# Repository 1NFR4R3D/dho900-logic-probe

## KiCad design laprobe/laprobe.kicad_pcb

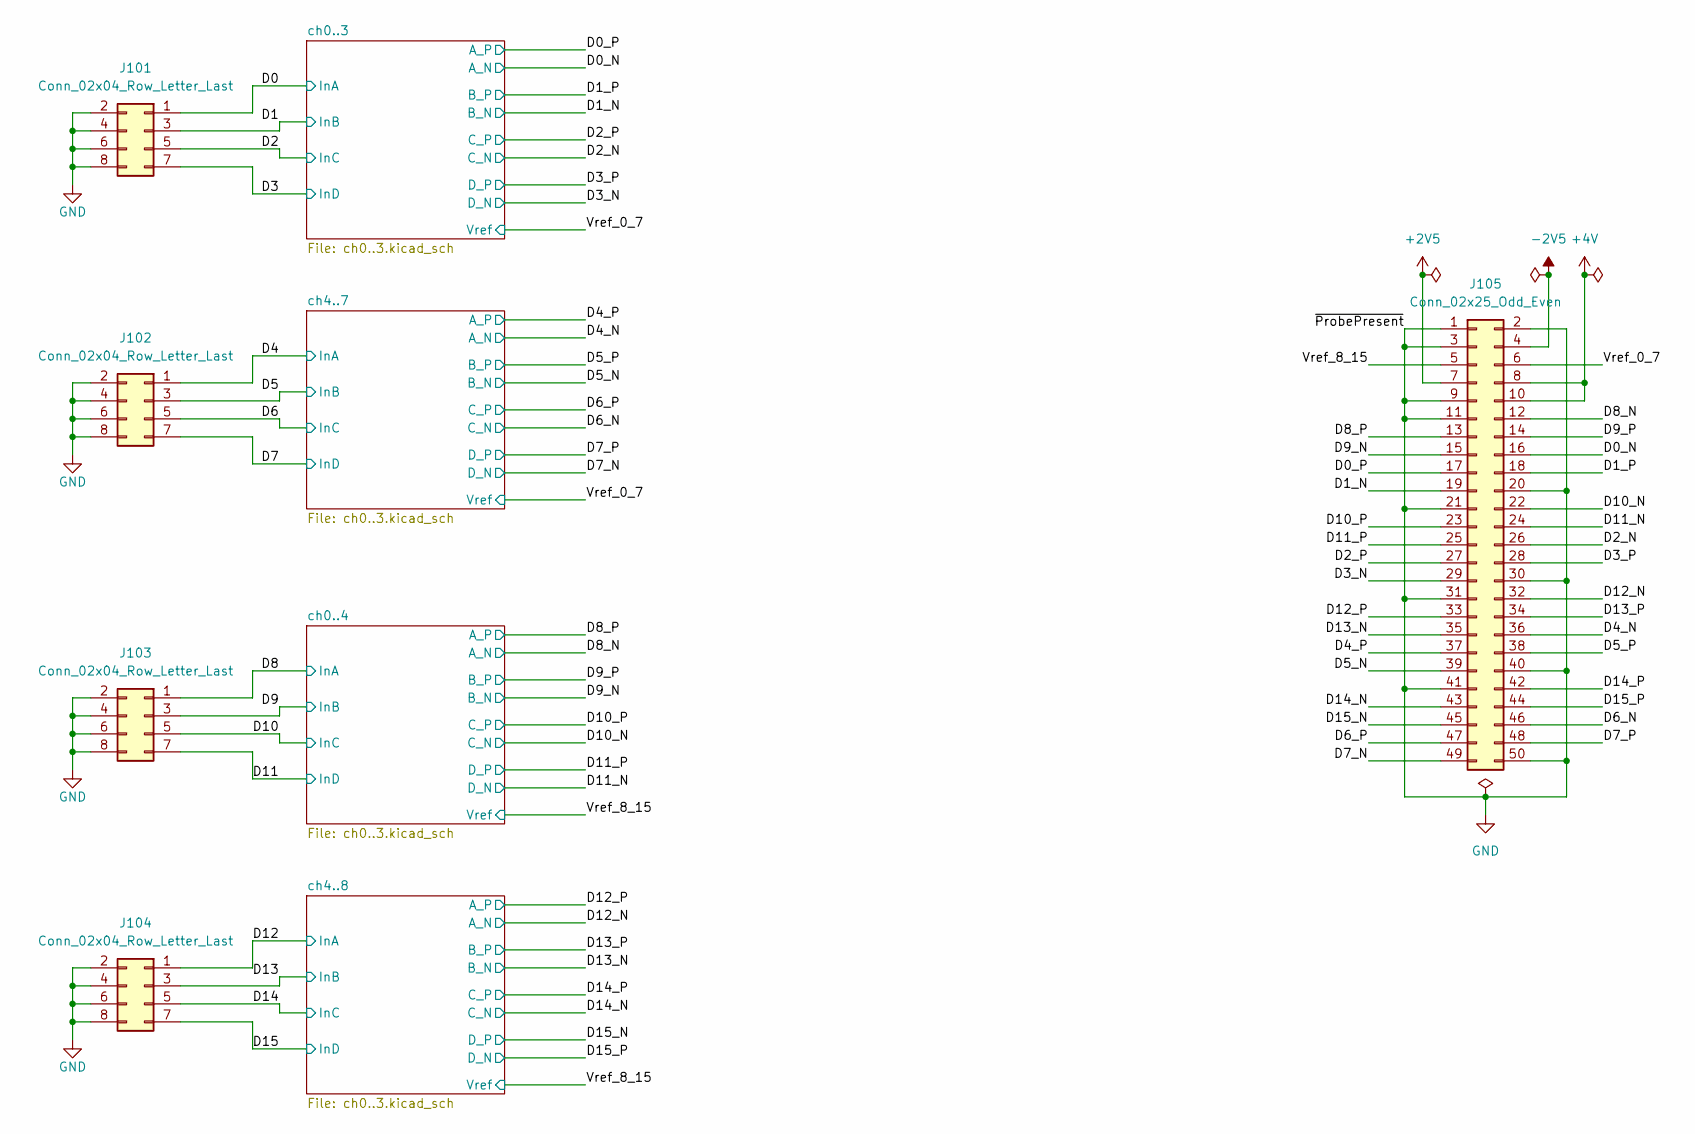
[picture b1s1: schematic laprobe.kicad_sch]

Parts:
J101, J102, J103, J104: Conn_02x04_Row_Letter_Last; PinHeader_2x04_P2.54mm_Vertical
J105: Conn_02x25_Odd_Even; IDC-Header_2x25_P2.54mm_Vertical

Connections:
+2V5: J105.7; also elsewhere on the board
+4V: J105.8, J105.10; also elsewhere on the board
-2V5: J105.4; also elsewhere on the board
/D0: J101.1; also elsewhere on the board
/D0_N: J105.16; also elsewhere on the board
/D0_P: J105.17; also elsewhere on the board
/D1: J101.3; also elsewhere on the board
/D1_N: J105.19; also elsewhere on the board
/D1_P: J105.18; also elsewhere on the board
/D2: J101.5; also elsewhere on the board
/D2_N: J105.26; also elsewhere on the board
/D2_P: J105.27; also elsewhere on the board
/D3: J101.7; also elsewhere on the board
/D3_N: J105.29; also elsewhere on the board
/D3_P: J105.28; also elsewhere on the board
/D4: J102.1; also elsewhere on the board
/D4_N: J105.36; also elsewhere on the board
/D4_P: J105.37; also elsewhere on the board
/D5: J102.3; also elsewhere on the board
/D5_N: J105.39; also elsewhere on the board
/D5_P: J105.38; also elsewhere on the board
/D6: J102.5; also elsewhere on the board
/D6_N: J105.46; also elsewhere on the board
/D6_P: J105.47; also elsewhere on the board
/D7: J102.7; also elsewhere on the board
/D7_N: J105.49; also elsewhere on the board
/D7_P: J105.48; also elsewhere on the board
/D8: J103.1; also elsewhere on the board
/D8_N: J105.12; also elsewhere on the board
/D8_P: J105.13; also elsewhere on the board
/D9: J103.3; also elsewhere on the board
/D9_N: J105.15; also elsewhere on the board
/D9_P: J105.14; also elsewhere on the board
/D10: J103.5; also elsewhere on the board
/D10_N: J105.22; also elsewhere on the board
/D10_P: J105.23; also elsewhere on the board
/D11: J103.7; also elsewhere on the board
/D11_N: J105.24; also elsewhere on the board
/D11_P: J105.25; also elsewhere on the board
/D12: J104.1; also elsewhere on the board
/D12_N: J105.32; also elsewhere on the board
/D12_P: J105.33; also elsewhere on the board
/D13: J104.3; also elsewhere on the board
/D13_N: J105.35; also elsewhere on the board
/D13_P: J105.34; also elsewhere on the board
/D14: J104.5; also elsewhere on the board
/D14_N: J105.43; also elsewhere on the board
/D14_P: J105.42; also elsewhere on the board
/D15: J104.7; also elsewhere on the board
/D15_N: J105.45; also elsewhere on the board
/D15_P: J105.44; also elsewhere on the board
/Vref_0_7: J105.6; also elsewhere on the board
/Vref_8_15: J105.5; also elsewhere on the board
GND: J101.2, J101.4, J101.6, J101.8, J102.2, J102.4, J102.6, J102.8, J103.2, J103.4, J103.6, J103.8, J104.2, J104.4, J104.6, J104.8, J105.1, J105.2, J105.3, J105.9, J105.11, J105.20, J105.21, J105.30, J105.31, J105.40, J105.41, J105.50; also elsewhere on the board

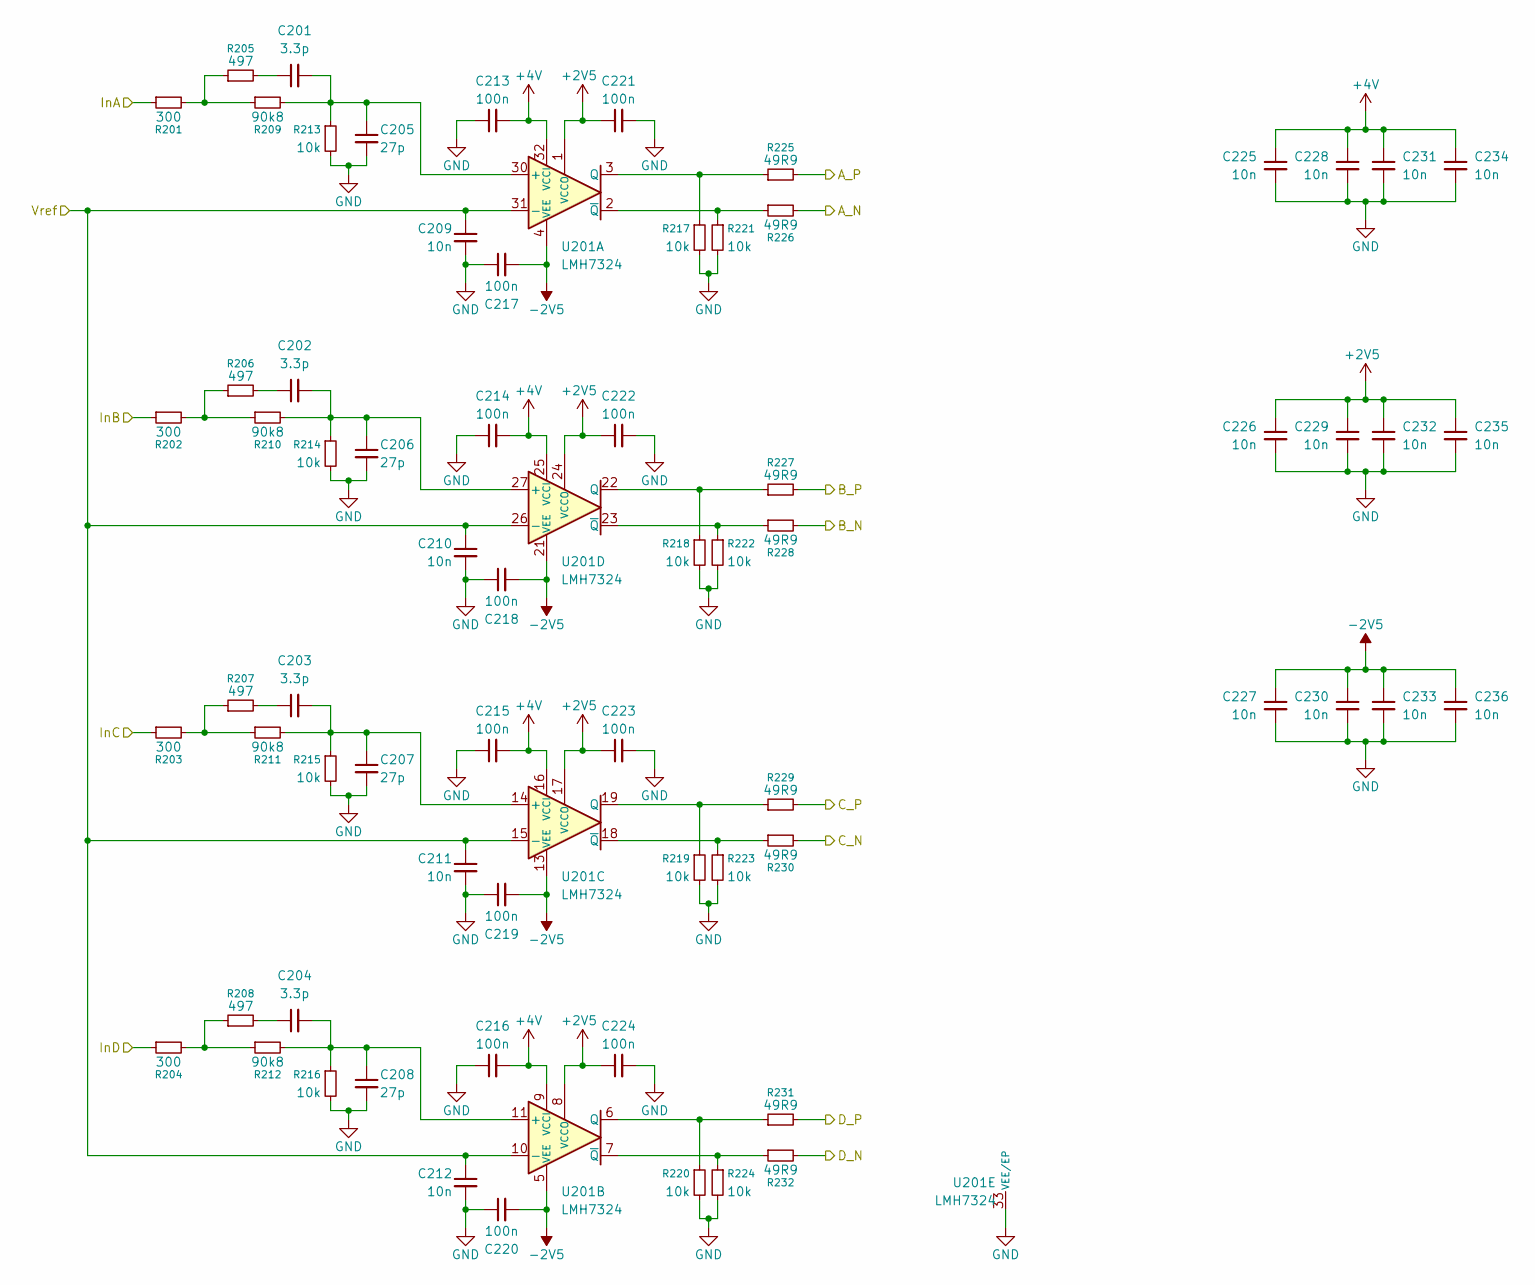
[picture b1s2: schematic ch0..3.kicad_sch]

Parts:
C201, C202, C203, C204: 3.3p; C_0603_1608Metric
C205, C206, C207, C208: 27p; C_0603_1608Metric
C209, C210, C211, C212, C225, C226, C227, C228, C229, C230, C231, C232, C233, C234, C235, C236: 10n; C_0603_1608Metric
C213, C214, C215, C216, C217, C218, C219, C220, C221, C222, C223, C224: 100n; C_0603_1608Metric
R201, R202, R203, R204: 300; R_0603_1608Metric
R205, R206, R207, R208: 497; R_0603_1608Metric
R209, R210, R211, R212: 90k8; R_0603_1608Metric
R213, R214, R215, R216, R217, R218, R219, R220, R221, R222, R223, R224: 10k; R_0603_1608Metric
R225, R226, R227, R228, R229, R230, R231, R232: 49R9; R_0603_1608Metric
U201: LMH7324; WQFN-32-1EP_5x5mm_P0.5mm_EP3.1x3.1mm

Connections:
+2V5: C221.1, C222.1, C223.1, C224.1, C226.1, C229.1, C232.1, C235.1, U201.1 (VCCO), U201.8 (VCCO), U201.17 (VCCO), U201.24 (VCCO); also elsewhere on the board
+4V: C213.2, C214.2, C215.2, C216.2, C225.1, C228.1, C231.1, C234.1, U201.9 (VCCI), U201.16 (VCCI), U201.25 (VCCI), U201.32 (VCCI); also elsewhere on the board
-2V5: C217.2, C218.2, C219.2, C220.2, C227.1, C230.1, C233.1, C236.1, U201.4 (VEE), U201.5 (VEE), U201.12 (VEE), U201.13 (VEE), U201.20 (VEE), U201.21 (VEE), U201.28 (VEE), U201.29 (VEE); also elsewhere on the board
/D0: R201.1; also elsewhere on the board
/D0_N: R226.2; also elsewhere on the board
/D0_P: R225.2; also elsewhere on the board
/D1: R202.1; also elsewhere on the board
/D1_N: R228.2; also elsewhere on the board
/D1_P: R227.2; also elsewhere on the board
/D2: R203.1; also elsewhere on the board
/D2_N: R230.2; also elsewhere on the board
/D2_P: R229.2; also elsewhere on the board
/D3: R204.1; also elsewhere on the board
/D3_N: R232.2; also elsewhere on the board
/D3_P: R231.2; also elsewhere on the board
/Vref_0_7: C209.1, C210.1, C211.1, C212.1, U201.10 (-), U201.15 (-), U201.26 (-), U201.31 (-); also elsewhere on the board
GND: C205.2, C206.2, C207.2, C208.2, C209.2, C210.2, C211.2, C212.2, C213.1, C214.1, C215.1, C216.1, C217.1, C218.1, C219.1, C220.1, C221.2, C222.2, C223.2, C224.2, C225.2, C226.2, C227.2, C228.2, C229.2, C230.2, C231.2, C232.2, C233.2, C234.2, C235.2, C236.2, R213.2, R214.2, R215.2, R216.2, R217.2, R218.2, R219.2, R220.2, R221.2, R222.2, R223.2, R224.2, U201.33 (VEE/EP); also elsewhere on the board
unnamed: C201.1, R205.2
unnamed: C202.1, R206.2
unnamed: C203.1, R207.2
unnamed: C204.1, R208.2
unnamed: R201.2, R205.1, R209.1
unnamed: R202.2, R206.1, R210.1
unnamed: R203.2, R207.1, R211.1
unnamed: R204.2, R208.1, R212.1
unnamed: C201.2, C205.1, R209.2, R213.1, U201.30 (+)
unnamed: R217.1, R225.1, U201.3 (Q)
unnamed: R221.1, R226.1, U201.2 (~Q)
unnamed: C204.2, C208.1, R212.2, R216.1, U201.11 (+)
unnamed: R220.1, R231.1, U201.6 (Q)
unnamed: R224.1, R232.1, U201.7 (~Q)
unnamed: C203.2, C207.1, R211.2, R215.1, U201.14 (+)
unnamed: R219.1, R229.1, U201.19 (Q)
unnamed: R223.1, R230.1, U201.18 (~Q)
unnamed: C202.2, C206.1, R210.2, R214.1, U201.27 (+)
unnamed: R218.1, R227.1, U201.22 (Q)
unnamed: R222.1, R228.1, U201.23 (~Q)

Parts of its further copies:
C301, C302, C303, C304, C401, C402, C403, C404, C501, C502, C503, C504: 3.3p; C_0603_1608Metric
C305, C306, C307, C308, C405, C406, C407, C408, C505, C506, C507, C508: 27p; C_0603_1608Metric
C309, C310, C311, C312, C325, C326, C327, C328, C329, C330, C331, C332, C333, C334, C335, C336, C409, C410, C411, C412, C425, C426, C427, C428, C429, C430, C431, C432, C433, C434, C435, C436, C509, C510, C511, C512, C525, C526, C527, C528, C529, C530, C531, C532, C533, C534, C535, C536: 10n; C_0603_1608Metric
C313, C314, C315, C316, C317, C318, C319, C320, C321, C322, C323, C324, C413, C414, C415, C416, C417, C418, C419, C420, C421, C422, C423, C424, C513, C514, C515, C516, C517, C518, C519, C520, C521, C522, C523, C524: 100n; C_0603_1608Metric
R301, R302, R303, R304, R401, R402, R403, R404, R501, R502, R503, R504: 300; R_0603_1608Metric
R305, R306, R307, R308, R405, R406, R407, R408, R505, R506, R507, R508: 497; R_0603_1608Metric
R309, R310, R311, R312, R409, R410, R411, R412, R509, R510, R511, R512: 90k8; R_0603_1608Metric
R313, R314, R315, R316, R317, R318, R319, R320, R321, R322, R323, R324, R413, R414, R415, R416, R417, R418, R419, R420, R421, R422, R423, R424, R513, R514, R515, R516, R517, R518, R519, R520, R521, R522, R523, R524: 10k; R_0603_1608Metric
R325, R326, R327, R328, R329, R330, R331, R332, R425, R426, R427, R428, R429, R430, R431, R432, R525, R526, R527, R528, R529, R530, R531, R532: 49R9; R_0603_1608Metric
U301, U401, U501: LMH7324; WQFN-32-1EP_5x5mm_P0.5mm_EP3.1x3.1mm

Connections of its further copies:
+2V5: C321.1, C322.1, C323.1, C324.1, C326.1, C329.1, C332.1, C335.1, C421.1, C422.1, C423.1, C424.1, C426.1, C429.1, C432.1, C435.1, C521.1, C522.1, C523.1, C524.1, C526.1, C529.1, C532.1, C535.1, U301.1 (VCCO), U301.8 (VCCO), U301.17 (VCCO), U301.24 (VCCO), U401.1 (VCCO), U401.8 (VCCO), U401.17 (VCCO), U401.24 (VCCO), U501.1 (VCCO), U501.8 (VCCO), U501.17 (VCCO), U501.24 (VCCO); also elsewhere on the board
+4V: C313.2, C314.2, C315.2, C316.2, C325.1, C328.1, C331.1, C334.1, C413.2, C414.2, C415.2, C416.2, C425.1, C428.1, C431.1, C434.1, C513.2, C514.2, C515.2, C516.2, C525.1, C528.1, C531.1, C534.1, U301.9 (VCCI), U301.16 (VCCI), U301.25 (VCCI), U301.32 (VCCI), U401.9 (VCCI), U401.16 (VCCI), U401.25 (VCCI), U401.32 (VCCI), U501.9 (VCCI), U501.16 (VCCI), U501.25 (VCCI), U501.32 (VCCI); also elsewhere on the board
-2V5: C317.2, C318.2, C319.2, C320.2, C327.1, C330.1, C333.1, C336.1, C417.2, C418.2, C419.2, C420.2, C427.1, C430.1, C433.1, C436.1, C517.2, C518.2, C519.2, C520.2, C527.1, C530.1, C533.1, C536.1, U301.4 (VEE), U301.5 (VEE), U301.12 (VEE), U301.13 (VEE), U301.20 (VEE), U301.21 (VEE), U301.28 (VEE), U301.29 (VEE), U401.4 (VEE), U401.5 (VEE), U401.12 (VEE), U401.13 (VEE), U401.20 (VEE), U401.21 (VEE), U401.28 (VEE), U401.29 (VEE), U501.4 (VEE), U501.5 (VEE), U501.12 (VEE), U501.13 (VEE), U501.20 (VEE), U501.21 (VEE), U501.28 (VEE), U501.29 (VEE); also elsewhere on the board
/D4: R301.1; also elsewhere on the board
/D4_N: R326.2; also elsewhere on the board
/D4_P: R325.2; also elsewhere on the board
/D5: R302.1; also elsewhere on the board
/D5_N: R328.2; also elsewhere on the board
/D5_P: R327.2; also elsewhere on the board
/D6: R303.1; also elsewhere on the board
/D6_N: R330.2; also elsewhere on the board
/D6_P: R329.2; also elsewhere on the board
/D7: R304.1; also elsewhere on the board
/D7_N: R332.2; also elsewhere on the board
/D7_P: R331.2; also elsewhere on the board
/D8: R401.1; also elsewhere on the board
/D8_N: R426.2; also elsewhere on the board
/D8_P: R425.2; also elsewhere on the board
/D9: R402.1; also elsewhere on the board
/D9_N: R428.2; also elsewhere on the board
/D9_P: R427.2; also elsewhere on the board
/D10: R403.1; also elsewhere on the board
/D10_N: R430.2; also elsewhere on the board
/D10_P: R429.2; also elsewhere on the board
/D11: R404.1; also elsewhere on the board
/D11_N: R432.2; also elsewhere on the board
/D11_P: R431.2; also elsewhere on the board
/D12: R501.1; also elsewhere on the board
/D12_N: R526.2; also elsewhere on the board
/D12_P: R525.2; also elsewhere on the board
/D13: R502.1; also elsewhere on the board
/D13_N: R528.2; also elsewhere on the board
/D13_P: R527.2; also elsewhere on the board
/D14: R503.1; also elsewhere on the board
/D14_N: R530.2; also elsewhere on the board
/D14_P: R529.2; also elsewhere on the board
/D15: R504.1; also elsewhere on the board
/D15_N: R531.2; also elsewhere on the board
/D15_P: R532.2; also elsewhere on the board
/Vref_0_7: C309.1, C310.1, C311.1, C312.1, U301.10 (-), U301.15 (-), U301.26 (-), U301.31 (-); also elsewhere on the board
/Vref_8_15: C409.1, C410.1, C411.1, C412.1, C509.1, C510.1, C511.1, C512.1, U401.10 (-), U401.15 (-), U401.26 (-), U401.31 (-), U501.10 (-), U501.15 (-), U501.26 (-), U501.31 (-); also elsewhere on the board
GND: C305.2, C306.2, C307.2, C308.2, C309.2, C310.2, C311.2, C312.2, C313.1, C314.1, C315.1, C316.1, C317.1, C318.1, C319.1, C320.1, C321.2, C322.2, C323.2, C324.2, C325.2, C326.2, C327.2, C328.2, C329.2, C330.2, C331.2, C332.2, C333.2, C334.2, C335.2, C336.2, C405.2, C406.2, C407.2, C408.2, C409.2, C410.2, C411.2, C412.2, C413.1, C414.1, C415.1, C416.1, C417.1, C418.1, C419.1, C420.1, C421.2, C422.2, C423.2, C424.2, C425.2, C426.2, C427.2, C428.2, C429.2, C430.2, C431.2, C432.2, C433.2, C434.2, C435.2, C436.2, C505.2, C506.2, C507.2, C508.2, C509.2, C510.2, C511.2, C512.2, C513.1, C514.1, C515.1, C516.1, C517.1, C518.1, C519.1, C520.1, C521.2, C522.2, C523.2, C524.2, C525.2, C526.2, C527.2, C528.2, C529.2, C530.2, C531.2, C532.2, C533.2, C534.2, C535.2, C536.2, R313.2, R314.2, R315.2, R316.2, R317.2, R318.2, R319.2, R320.2, R321.2, R322.2, R323.2, R324.2, R413.2, R414.2, R415.2, R416.2, R417.2, R418.2, R419.2, R420.2, R421.2, R422.2, R423.2, R424.2, R513.2, R514.2, R515.2, R516.2, R517.2, R518.2, R519.2, R520.2, R521.2, R522.2, R523.2, R524.2, U301.33 (VEE/EP), U401.33 (VEE/EP), U501.33 (VEE/EP); also elsewhere on the board
unnamed: C301.1, R305.2
unnamed: C302.1, R306.2
unnamed: C303.1, R307.2
unnamed: C304.1, R308.2
unnamed: C401.1, R405.2
unnamed: C402.1, R406.2
unnamed: C403.1, R407.2
unnamed: C404.1, R408.2
unnamed: C501.1, R505.2
unnamed: C502.1, R506.2
unnamed: C503.1, R507.2
unnamed: C504.1, R508.2
unnamed: R301.2, R305.1, R309.1
unnamed: R302.2, R306.1, R310.1
unnamed: R303.2, R307.1, R311.1
unnamed: R304.2, R308.1, R312.1
unnamed: R401.2, R405.1, R409.1
unnamed: R402.2, R406.1, R410.1
unnamed: R403.2, R407.1, R411.1
unnamed: R404.2, R408.1, R412.1
unnamed: R501.2, R505.1, R509.1
unnamed: R502.2, R506.1, R510.1
unnamed: R503.2, R507.1, R511.1
unnamed: R504.2, R508.1, R512.1
unnamed: C301.2, C305.1, R309.2, R313.1, U301.30 (+)
unnamed: R317.1, R325.1, U301.3 (Q)
unnamed: R321.1, R326.1, U301.2 (~Q)
unnamed: C304.2, C308.1, R312.2, R316.1, U301.11 (+)
unnamed: R320.1, R331.1, U301.6 (Q)
unnamed: R324.1, R332.1, U301.7 (~Q)
unnamed: C303.2, C307.1, R311.2, R315.1, U301.14 (+)
unnamed: R319.1, R329.1, U301.19 (Q)
unnamed: R323.1, R330.1, U301.18 (~Q)
unnamed: C302.2, C306.1, R310.2, R314.1, U301.27 (+)
unnamed: R318.1, R327.1, U301.22 (Q)
unnamed: R322.1, R328.1, U301.23 (~Q)
unnamed: C401.2, C405.1, R409.2, R413.1, U401.30 (+)
unnamed: R417.1, R425.1, U401.3 (Q)
unnamed: R421.1, R426.1, U401.2 (~Q)
unnamed: C404.2, C408.1, R412.2, R416.1, U401.11 (+)
unnamed: R420.1, R431.1, U401.6 (Q)
unnamed: R424.1, R432.1, U401.7 (~Q)
unnamed: C403.2, C407.1, R411.2, R415.1, U401.14 (+)
unnamed: R419.1, R429.1, U401.19 (Q)
unnamed: R423.1, R430.1, U401.18 (~Q)
unnamed: C402.2, C406.1, R410.2, R414.1, U401.27 (+)
unnamed: R418.1, R427.1, U401.22 (Q)
unnamed: R422.1, R428.1, U401.23 (~Q)
unnamed: C501.2, C505.1, R509.2, R513.1, U501.30 (+)
unnamed: R517.1, R525.1, U501.3 (Q)
unnamed: R521.1, R526.1, U501.2 (~Q)
unnamed: C504.2, C508.1, R512.2, R516.1, U501.11 (+)
unnamed: R520.1, R531.1, U501.6 (Q)
unnamed: R524.1, R532.1, U501.7 (~Q)
unnamed: C503.2, C507.1, R511.2, R515.1, U501.14 (+)
unnamed: R519.1, R529.1, U501.19 (Q)
unnamed: R523.1, R530.1, U501.18 (~Q)
unnamed: C502.2, C506.1, R510.2, R514.1, U501.27 (+)
unnamed: R518.1, R527.1, U501.22 (Q)
unnamed: R522.1, R528.1, U501.23 (~Q)

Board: 2 copper layers, 281 parts (12 on the bottom side), 134 nets, no tracks yet.

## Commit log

2025-11-30 Switch around some channels on buffer/tranceiver for routing
2025-11-30 Checkpoint: All but frozen ch0
2025-11-30 Remove replicate_layout.log
